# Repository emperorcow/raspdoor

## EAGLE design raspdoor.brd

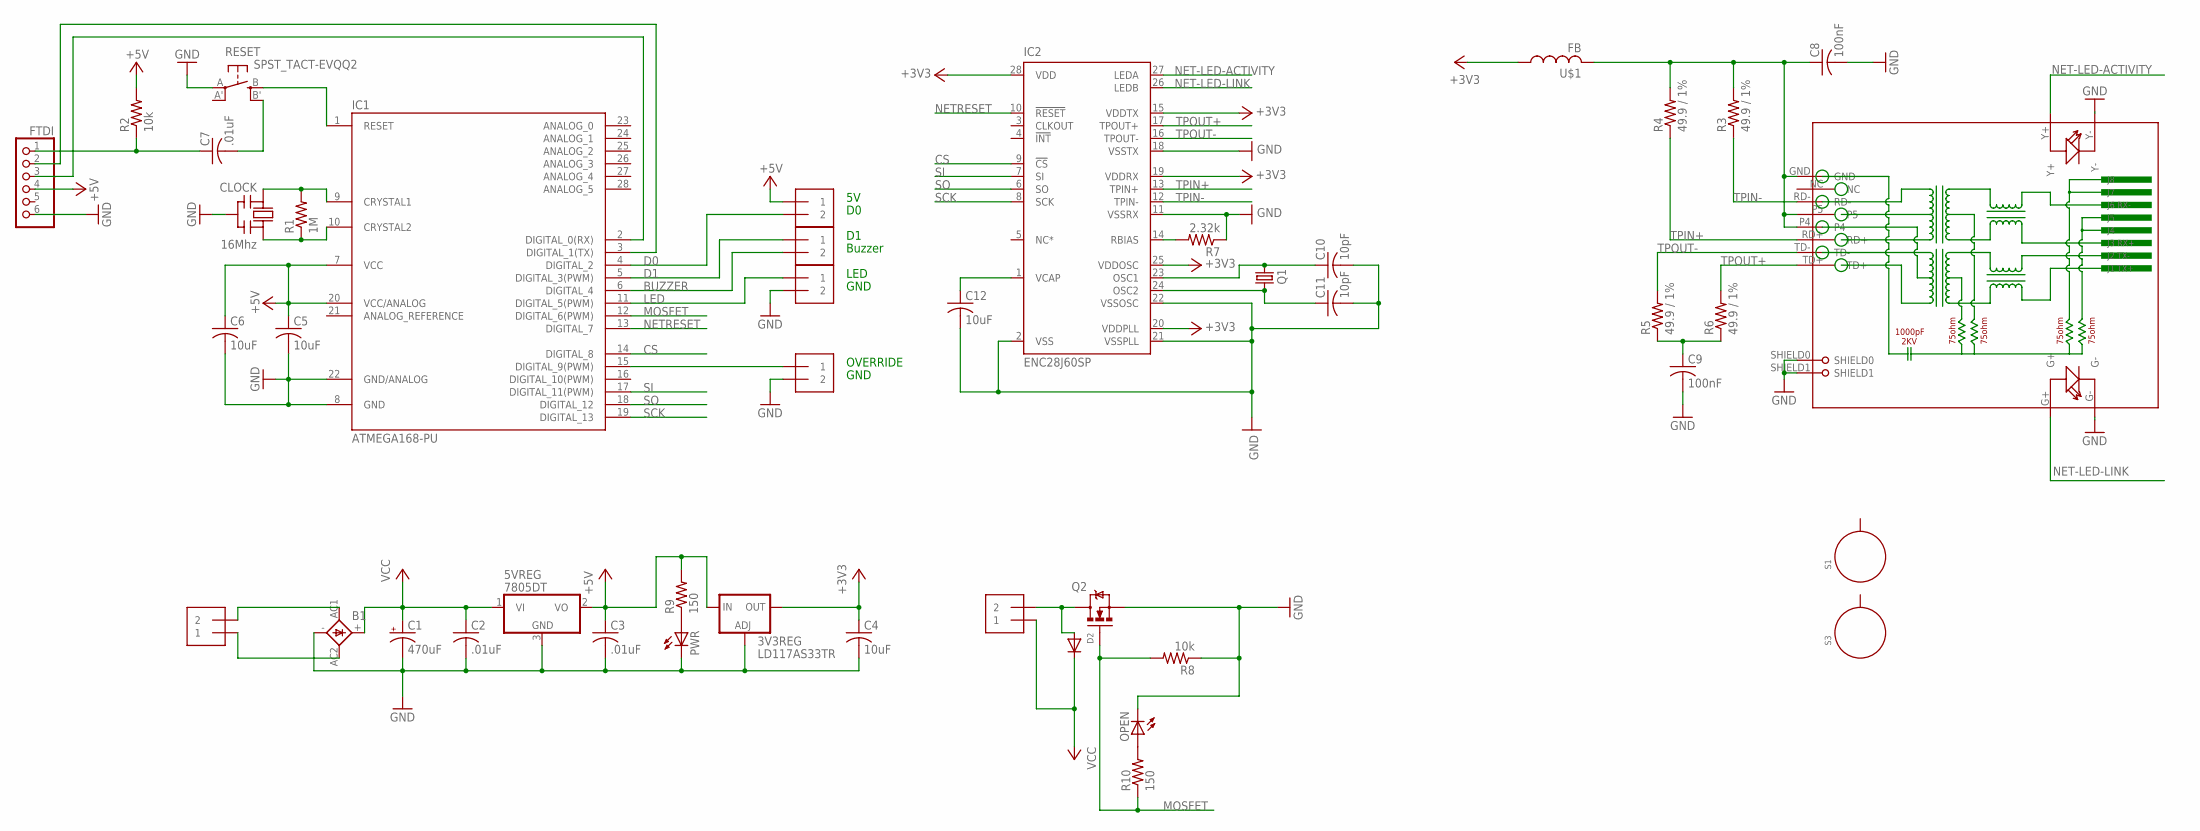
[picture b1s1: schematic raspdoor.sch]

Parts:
3V3REG: LD117AS33TR; SOT223
5VREG: 7805DT; TO252
B1: 2KBB
C1: 470uF; 153CLV-0810
C2, C3, C7: .01uF; C0805
C4, C5, C6, C12: 10uF; C0805
C8, C9: 100nF; C0805
C10, C11: 10pF; C0805
CLOCK: 16Mhz; CERM_OSC
D2: DIODESMA; SMADIODE
FTDI: PINHD-1X6; 1X06
IC1: ATMEGA168-PU; DIL28-3
IC2: ENC28J60SP; DIL28-3
J1, J2, J3, J4, J5, J6: 1X2-3.5MM
OPEN: LEDCHIPLED_0805; CHIPLED_0805
PWR: LEDCHIPLED_0805; CHIPLED_0805
Q1: CRYSTALHC49S; HC49/S
Q2: MOSFET-NCHANNELFQP30N06L; TO220V
R1: 1M; R0805
R2, R8: 10k; R0805
R3, R4, R5, R6: 49.9 / 1%; R0805
R7: 2.32k; R0805
R9, R10: 150; R0805
RESET: SPST_TACT-EVQQ2; EVQ-Q2
RJ1: HR911105A
S1, S3: STANDOFF_ELECTRICAL; STANDOFF-ELECTRICAL
U$1: FB

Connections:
+3V3: 3V3REG.4 (OUT), C4.1, IC2.15 (VDDTX), IC2.19 (VDDRX), IC2.20 (VDDPLL), IC2.25 (VDDOSC), IC2.28 (VDD), U$1.P$1 (1)
+5V: 3V3REG.3 (IN), 5VREG.2 (VO), C3.1, C5.1, C6.1, FTDI.4, IC1.7 (VCC), IC1.20 (VCC/ANALOG), J3.1, R2.2, R9.2
AC1: B1.AC1, J1.2
AC2: B1.AC2, J1.1
BUZZER: IC1.6 (DIGITAL_4), J4.2
CS: IC1.14 (DIGITAL_8), IC2.9 (!CS)
D0: IC1.4 (DIGITAL_2), J3.2
D1: IC1.5 (DIGITAL_3(PWM)), J4.1
GND: 3V3REG.1 (ADJ), 5VREG.3 (GND), B1.-, C1.-, C2.2, C3.2, C4.2, C5.2, C6.2, C8.2, C9.2, C10.2, C11.2, C12.2, CLOCK.P$2 (GND), FTDI.6, IC1.8 (GND), IC1.22 (GND/ANALOG), IC2.2 (VSS), IC2.11 (VSSRX), IC2.18 (VSSTX), IC2.21 (VSSPLL), IC2.22 (VSSOSC), J5.2, J6.2, OPEN.C, PWR.C, Q2.3 (S), R7.1, R8.1, RESET.A, RJ1.G-, RJ1.SHIELD0, RJ1.SHIELD1, RJ1.Y-
LED: IC1.11 (DIGITAL_5(PWM)), J5.1
MOSFET: IC1.12 (DIGITAL_6(PWM)), Q2.1 (G), R8.2, R10.1
unnamed: IC1.1 (RESET), RESET.B (S)
unnamed: C7.2, RESET.B' (S1)
unnamed: C7.1, FTDI.1, R2.1
unnamed: FTDI.2, IC1.3 (DIGITAL_1(TX))
unnamed: CLOCK.P$1 (IN), IC1.9 (CRYSTAL1), R1.2
unnamed: CLOCK.P$3 (OUT), IC1.10 (CRYSTAL2), R1.1
unnamed: FTDI.3, IC1.2 (DIGITAL_0(RX))
unnamed: C8.1, R3.2, R4.2, RJ1.GND, RJ1.P4, RJ1.P5, U$1.P$2 (2)
unnamed: IC2.14 (RBIAS), R7.2
unnamed: C10.1, IC2.23 (OSC1), Q1.1
unnamed: C11.1, IC2.24 (OSC2), Q1.2
unnamed: C12.1, IC2.1 (VCAP)
unnamed: C9.1, R5.1, R6.1
unnamed: D2.A, J2.2, Q2.2 (D)
unnamed: PWR.A, R9.1
unnamed: OPEN.A, R10.2
unnamed: IC1.15 (DIGITAL_9(PWM)), J6.1
NET-LED-ACTIVITY: IC2.27 (LEDA), RJ1.Y+
NET-LED-LINK: IC2.26 (LEDB), RJ1.G+
NETRESET: IC1.13 (DIGITAL_7), IC2.10 (!RESET)
SCK: IC1.19 (DIGITAL_13), IC2.8 (SCK)
SI: IC1.17 (DIGITAL_11(PWM)), IC2.7 (SI)
SO: IC1.18 (DIGITAL_12), IC2.6 (SO)
TPIN+: IC2.13 (TPIN+), R4.1, RJ1.RD+
TPIN-: IC2.12 (TPIN-), R3.1, RJ1.RD-
TPOUT+: IC2.17 (TPOUT+), R6.2, RJ1.TD+
TPOUT-: IC2.16 (TPOUT-), R5.2, RJ1.TD-
VCC: 5VREG.1 (VI), B1.+, C1.+, C2.1, D2.C, J2.1

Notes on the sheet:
Buzzer
LED
GND
OVERRIDE

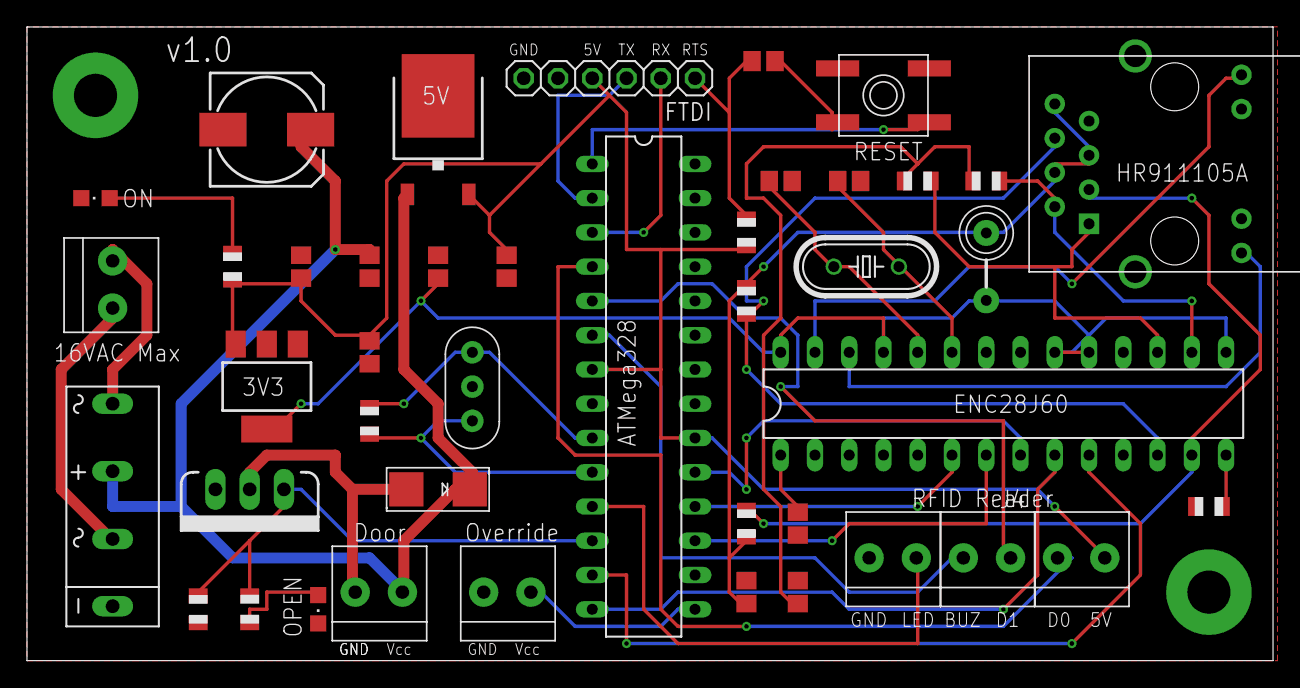
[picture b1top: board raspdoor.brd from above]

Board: 2 copper layers, 92.4 x 47.0 mm, 45 parts (0 on the bottom side), 39 nets.

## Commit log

2014-03-17 Upload Board
2014-03-25 Added ENC28J60 connections to board
2014-03-28 Minor changes
2014-04-07 Initial Board + RFID Terminals
2014-05-08 Added an override button to schematic and PCB.
    Allows for the hookup of a switch that will override RFID and cause
    action in code immediately.

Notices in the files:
parts and their libraries:
SparkFun-DiscreteSemi: Licensing: Creative Commons ShareAlike 4.0 International - https://creativecommons.org/licenses/by-sa/4.0
